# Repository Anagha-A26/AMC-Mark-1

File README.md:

# AMC-Mark-1
KiCad-based 2-layer STM32F401RE evaluation board with USB, UART, SPI, I²C, SWD, GPIO expansion, power regulation and user interfaces.

**STM32F401RE DEVELOPMENT BOARD**

**1. Selected MCU & Design Concept**

**Selected MCU**

**STM32F401RE / STM32F401RET6**

The **STM32F401RE** is selected as the core microcontroller for the evaluation board. It is based on an **Arm Cortex-M4 processor with Floating Point Unit (FPU)** and provides a broad set of peripherals, including GPIO, timers, ADC, UART/USART, SPI, I²C, USB 2.0 Full-Speed and SWD/JTAG debugging capabilities.
The MCU was selected because its peripheral set allows the major requirements of the evaluation board to be implemented around a **single central processing device**, while providing sufficient GPIO for external expansion.

**Why STM32F401RE?**

The core objective is to develop a **compact evaluation platform around the STM32F401RE** that allows users to:

- Program and debug the MCU through SWD.
- Communicate with a PC or USB host through USB.
- Experiment with UART, SPI and I²C peripherals.
- Access additional GPIOs for external circuits and modules.
- Interact with the board through user buttons and LEDs.
- Evaluate the MCU in a practical embedded-system development environment.

Thus, the STM32F401RE acts as the **central hub connecting the processing, communication, debugging and expansion interfaces**.

**Design Concept**

We propose a **compact, custom 2-layer STM32F401RE evaluation board** designed to provide convenient access to the MCU's processing, communication, debugging and GPIO capabilities.
The design is **functionally inspired by the STM32 NUCLEO-F401RE**, which provides STM32 development, Arduino compatibility, ST Morpho expansion and integrated ST-LINK debugging.
However, instead of reproducing the Nucleo architecture, our design independently implements the required functionality with a simpler and more focused architecture.

**Key design approach**

- **STM32F401RE** as the central MCU.
- **External ST-Link through SWD**, avoiding duplication of the on-board ST-LINK circuitry.
- **USB Type-C** providing direct USB 2.0 connectivity to the STM32.
- Dedicated and clearly labelled **UART, SPI and I²C interfaces**.
- **GPIO expansion headers** for external experimentation.
- Dedicated **reset button, user button, user LED and power indication**.
- Custom **power distribution, decoupling and grounding strategy**.
- Independently designed **2-layer PCB layout and routing** within the competition's 100 mm × 100 mm limit.

**Core Design Idea**

> To create a compact and accessible STM32F401RE evaluation platform that brings the MCU's major communication, debugging and GPIO capabilities onto a single independently designed 2-layer PCB, allowing users to program, debug and experiment with the MCU and external peripherals without reproducing the complete Nucleo architecture.

---

**Design Objectives**

1. Develop a functional **STM32F401RE evaluation platform**.
2. Provide **USB Type-C USB 2.0 connectivity** to the MCU.
3. Provide accessible **UART, SPI and I²C interfaces**.
4. Provide **SWD programming and debugging** using an external programmer/debugger.
5. Provide **user reset, user button, user LED and power indication**.
6. Provide **GPIO expansion headers** with power and ground.
7. Implement appropriate **power regulation and local decoupling**.
8. Develop a compact and electrically complete **2-layer PCB within 100 mm × 100 mm**.
9. Independently design the **schematic, component selection, placement, routing and silkscreen** rather than reproducing the reference board.

**2. BLOCK DIAGRAM**

**3. Schematic progress**

[View Schematic and PCB PDF](./schematic_pcb.pdf)

**4. Components Used**

| **Sl. No.** | **Component Type**     | **Value / Part Number**         | **Quantity** | **Section / Function**          |
| ----------- | ---------------------- | ------------------------------- | ------------ | ------------------------------- |
| 1           | Microcontroller        | STM32F401RET6                   | 1            | Main MCU                        |
| 2           | Voltage Regulator      | AMS1117-3.3                     | 1            | 5 V to 3.3 V regulation         |
| 3           | USB Type-C Connector   | USB\_C\_Receptacle\_USB2.0\_16P | 1            | USB communication and 5 V input |
| 4           | Pin Header / Connector | Conn\_01x02\_Pin                | 1            | External 5 V / GND connection   |
| 5           | Pin Header             | Conn\_01x05\_Pin                | 1            | SWD programming/debugging       |
| 6           | Pin Header             | Conn\_01x04\_Pin                | 1            | UART interface                  |
| 7           | Pin Header             | Conn\_01x06\_Pin                | 1            | SPI interface                   |
| 8           | Pin Header             | Conn\_01x04\_Pin                | 1            | I²C interface                   |
| 9           | Pin Header             | Conn\_01x10\_Pin                | 1            | GPIO expansion                  |
| 10          | Push Button            | SW\_Push                        | 1            | User button                     |
| 11          | Push Button            | SW\_Push                        | 1            | Reset button                    |
| 12          | LED                    | LED                             | 1            | Power ON indicator              |
| 13          | LED                    | LED                             | 1            | User-programmable LED           |
| 14          | Resistor               | 4.7 kΩ                          | 1            | I²C SCL pull-up                 |
| 15          | Resistor               | 4.7 kΩ                          | 1            | I²C SDA pull-up                 |
| 16          | Resistor               | 1 kΩ                            | 1            | Power LED current limiting      |
| 17          | Resistor               | 330 Ω                           | 1            | User LED current limiting       |
| 18          | Resistor               | 10 kΩ                           | 1            | BOOT0 pull-down                 |
| 19          | Resistor               | 10 kΩ                           | 1            | User button pull-up             |
| 20          | Resistor               | 10 kΩ                           | 1            | NRST pull-up                    |
| 21          | Resistor               | 5.1 kΩ                          | 1            | USB-C CC1 pull-down             |
| 22          | Resistor               | 5.1 kΩ                          | 1            | USB-C CC2 pull-down             |
| 23          | Capacitor              | 10 µF                           | 1            | AMS1117 input capacitor         |
| 24          | Capacitor              | 10 µF                           | 1            | AMS1117 output capacitor        |
| 25          | Power Multiplexer      | TPS2116DRLR                     | 1            | Priority selection between USB-C 5 V and external 5 V power inputs |

**5. Major design decisions**

- Selected USB Type-C as the USB connector for communication and power input.
- Designed the board to accept 5 V power from either USB-C or an external 5 V connector.
- Selected the AMS1117-3.3 voltage regulator to generate the required 3.3 V supply.
- Used an external ST-Link through the SWD header instead of including an onboard ST-Link debugger.
- Selected PA11 and PA12 for USB D− and D+ communication.
- Selected PA9 and PA10 for UART TX and RX.
- Selected PA4, PA5, PA6 and PA7 for SPI communication.
- Selected PB6 and PB7 for I²C communication.
- Used 4.7 kΩ pull-up resistors for the I²C SCL and SDA lines.
- Used 5.1 kΩ pull-down resistors on CC1 and CC2 to configure the USB-C connector for device operation.
- Pulled BOOT0 to GND using a 10 kΩ resistor to ensure normal boot from internal Flash memory.
- Used separate headers for UART, SPI, I²C, SWD and GPIO expansion for easier testing and external interfacing.
- Selected additional unused MCU pins and brought them out through a dedicated GPIO expansion header.
- Used separate Power ON LED and User LED to distinguish power status from software-controlled indication.
- Chose a simple push-button reset circuit with a pull-up resistor for reliable manual reset.

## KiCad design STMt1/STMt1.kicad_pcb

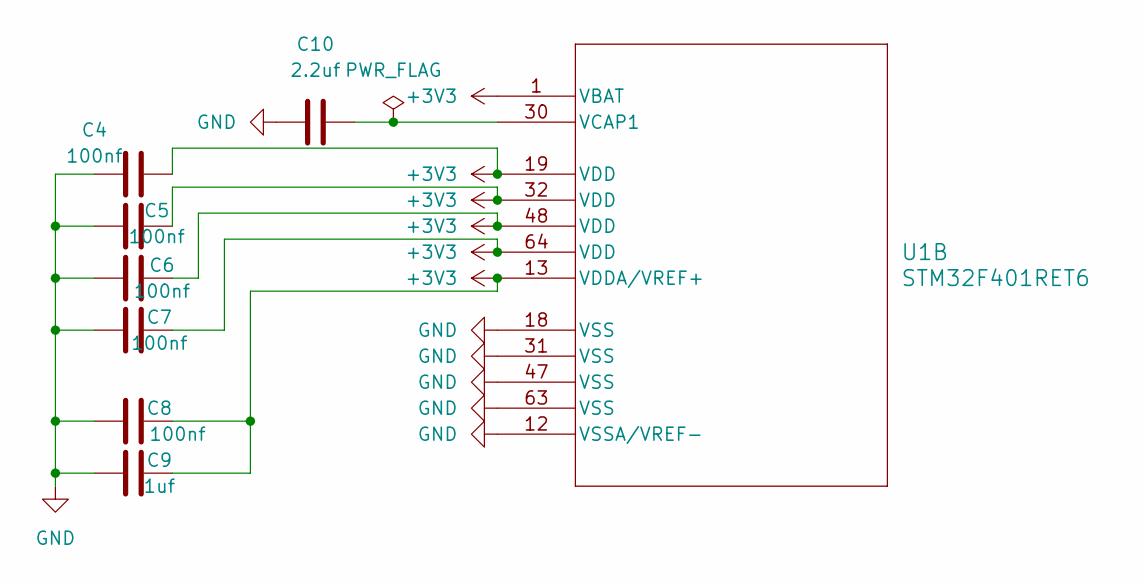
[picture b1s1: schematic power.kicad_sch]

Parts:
C4, C5, C6, C7, C8: 100nf; C_0603_1608Metric
C9: 1uf; C_0603_1608Metric
C10: 2.2uf; C_0603_1608Metric
U1: STM32F401RET6; QFP50P1200X1200X160-64N

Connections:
+3V3: C4.2, C5.2, C6.2, C7.2, C8.2, C9.2, U1.1 (VBAT), U1.13 (VDDA/VREF+), U1.19 (VDD), U1.32 (VDD), U1.48 (VDD), U1.64 (VDD); also elsewhere on the board
GND: C4.1, C5.1, C6.1, C7.1, C8.1, C9.1, C10.1, U1.12 (VSSA/VREF-), U1.18 (VSS), U1.31 (VSS), U1.47 (VSS), U1.63 (VSS); also elsewhere on the board
unnamed 36: C10.2, U1.30 (VCAP1); also elsewhere on the board

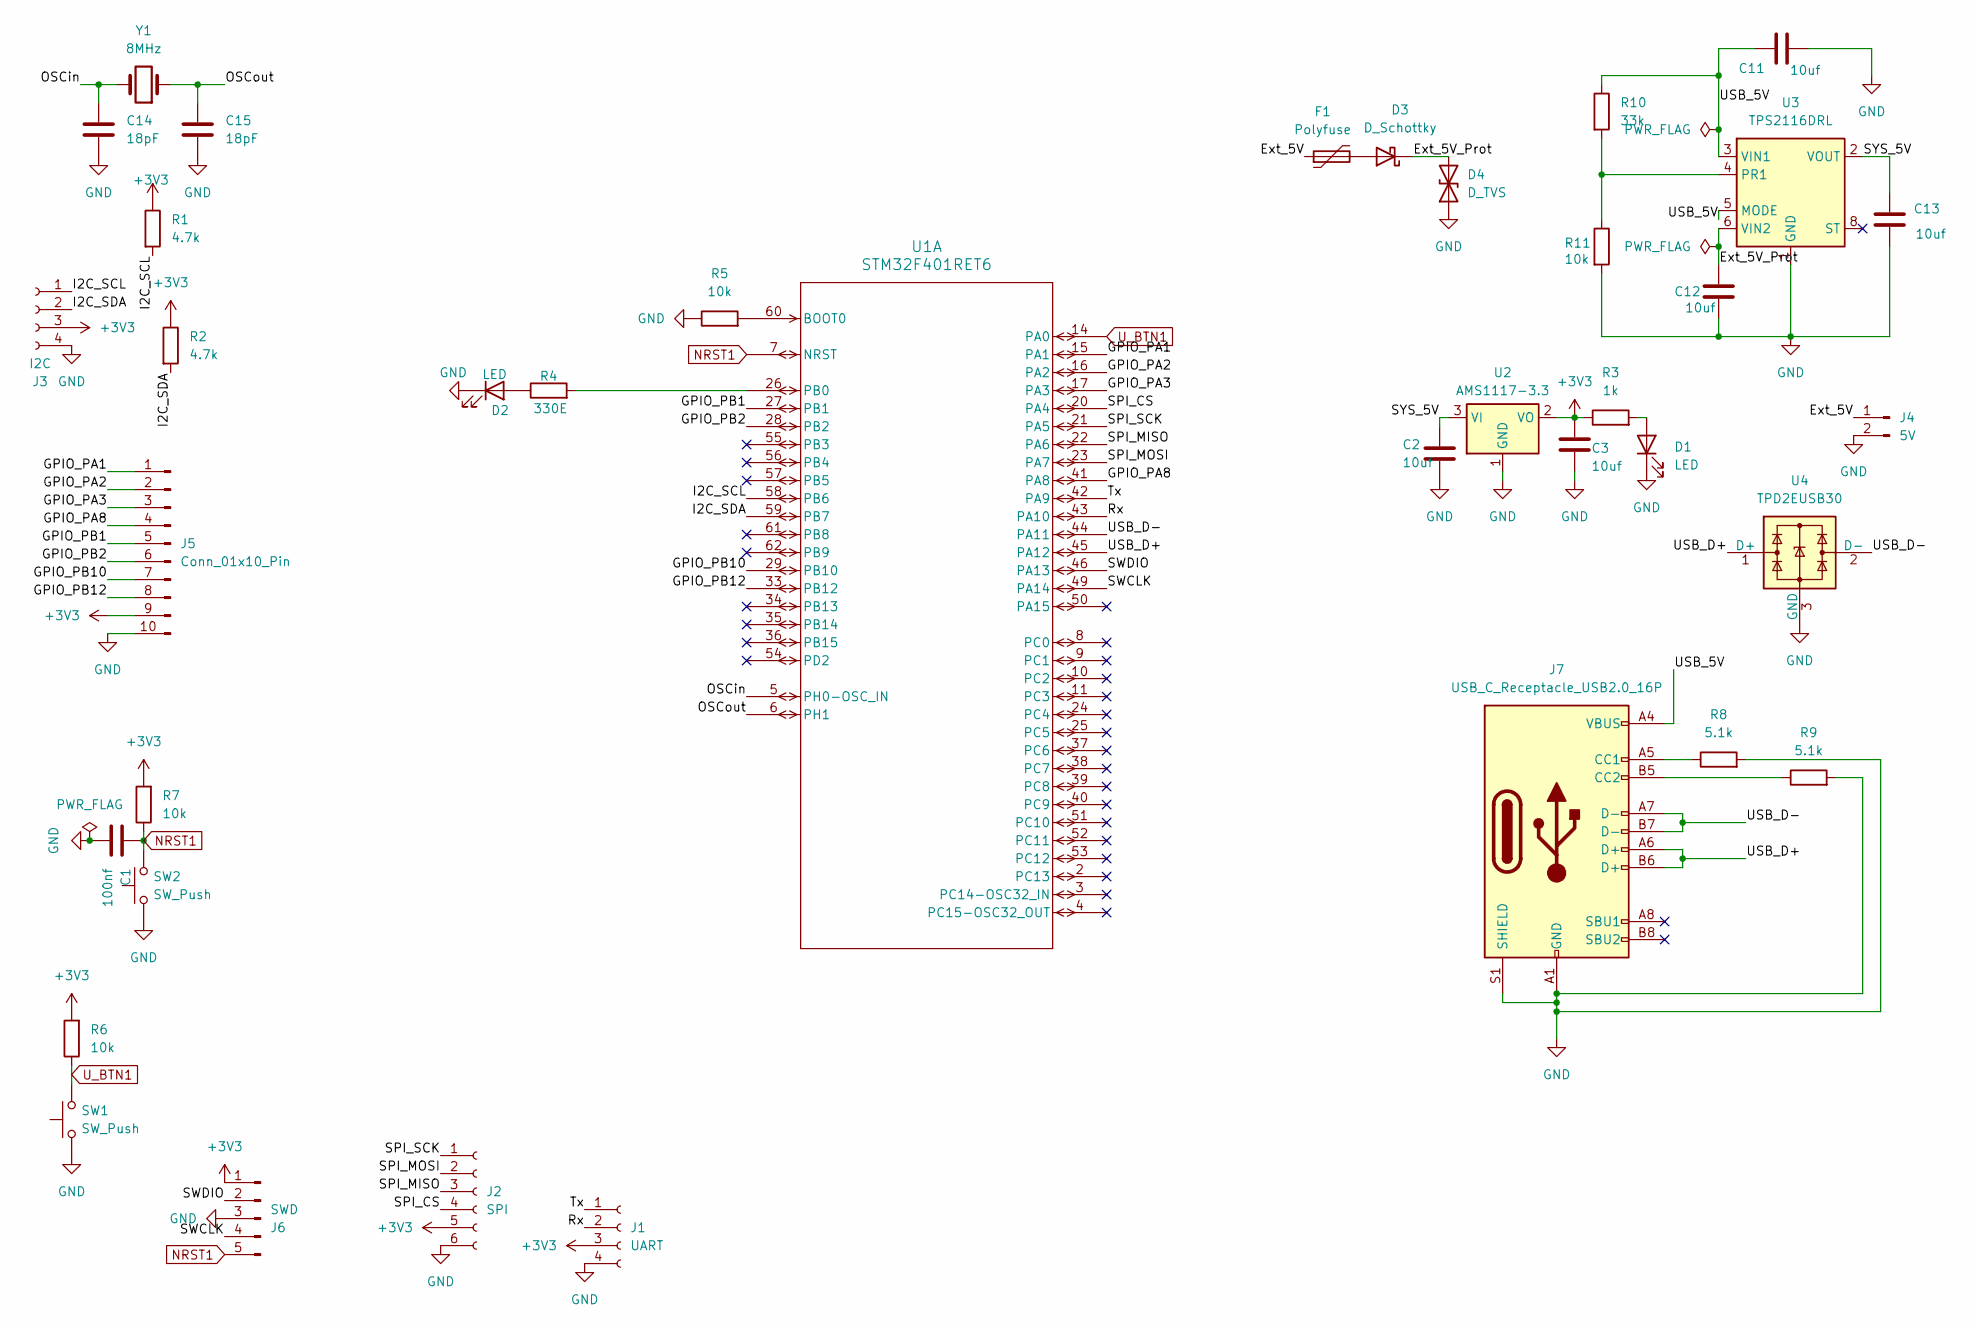
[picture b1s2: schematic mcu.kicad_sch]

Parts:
C1: 100nf; C_0603_1608Metric
C2, C3, C11, C12, C13: 10uf; C_0603_1608Metric
C14, C15: 18pF; C_0603_1608Metric
D1, D2: LED; LED_0603_1608Metric
D3: D_Schottky; SODFL3618X110N
D4: D_TVS; D_1206_3216Metric
F1: Polyfuse; Fuse_1206_3216Metric
J1: UART; PinSocket_1x04_P2.54mm_Vertical
J2: SPI; PinSocket_1x06_P2.54mm_Vertical
J3: I2C; PinSocket_1x04_P2.54mm_Vertical
J4: 5V; PinSocket_1x02_P2.54mm_Vertical
J5: Conn_01x10_Pin; PinSocket_1x10_P2.54mm_Vertical
J6: SWD; PinSocket_1x05_P2.54mm_Vertical
J7: USB_C_Receptacle_USB2.0_16P; USB_C_Receptacle_G-Switch_GT-USB-7010ASV
R1, R2: 4.7k; R_0603_1608Metric
R3: 1k; R_0603_1608Metric
R4: 330E; R_0603_1608Metric
R5, R6, R7, R11: 10k; R_0603_1608Metric
R8, R9: 5.1k; R_0603_1608Metric
R10: 33k; R_0603_1608Metric
SW1, SW2: SW_Push; SW_Push_1P1T_NO_CK_KMR2
U1: STM32F401RET6; QFP50P1200X1200X160-64N
U2: AMS1117-3.3; SOT-223-3_TabPin2
U3: TPS2116DRL; SOTFL50P160X60-8N
U4: TPD2EUSB30; SOTFL35P100X50-3N
Y1: 8MHz; Crystal_SMD_0603-2Pin_6.0x3.5mm

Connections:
+3V3: C3.1, J1.3, J2.5, J3.3, J5.9, J6.1, R1.1, R2.1, R3.1, R6.2, R7.2, U2.2 (VO); also elsewhere on the board
/MCU/Ext_5V: F1.1, J4.1
/MCU/Ext_5V_Prot: C12.1, D3.1 (K), D4.2 (A2), U3.6 (VIN2)
/MCU/GPIO_PA1: J5.1, U1.15 (PA1); also elsewhere on the board
/MCU/GPIO_PA2: J5.2, U1.16 (PA2); also elsewhere on the board
/MCU/GPIO_PA3: J5.3, U1.17 (PA3); also elsewhere on the board
/MCU/GPIO_PA8: J5.4, U1.41 (PA8); also elsewhere on the board
/MCU/GPIO_PB1: J5.5, U1.27 (PB1); also elsewhere on the board
/MCU/GPIO_PB2: J5.6, U1.28 (PB2); also elsewhere on the board
/MCU/GPIO_PB10: J5.7, U1.29 (PB10); also elsewhere on the board
/MCU/GPIO_PB12: J5.8, U1.33 (PB12); also elsewhere on the board
/MCU/I2C_SCL: J3.1, R1.2, U1.58 (PB6); also elsewhere on the board
/MCU/I2C_SDA: J3.2, R2.2, U1.59 (PB7); also elsewhere on the board
/MCU/OSCin: C14.1, U1.5 (PH0-OSC_IN), Y1.2; also elsewhere on the board
/MCU/OSCout: C15.1, U1.6 (PH1), Y1.1; also elsewhere on the board
/MCU/Rx: J1.2, U1.43 (PA10); also elsewhere on the board
/MCU/SPI_CS: J2.4, U1.20 (PA4); also elsewhere on the board
/MCU/SPI_MISO: J2.3, U1.22 (PA6); also elsewhere on the board
/MCU/SPI_MOSI: J2.2, U1.23 (PA7); also elsewhere on the board
/MCU/SPI_SCK: J2.1, U1.21 (PA5); also elsewhere on the board
/MCU/SWCLK: J6.4, U1.49 (PA14); also elsewhere on the board
/MCU/SWDIO: J6.2, U1.46 (PA13); also elsewhere on the board
/MCU/SYS_5V: C2.1, C13.1, U2.3 (VI), U3.2 (VOUT), U3.7 (VOUT)
/MCU/Tx: J1.1, U1.42 (PA9); also elsewhere on the board
/MCU/USB_5V: C11.1, J7.A4 (VBUS), J7.A9 (VBUS), J7.B4 (VBUS), J7.B9 (VBUS), R10.1, U3.3 (VIN1), U3.5 (MODE)
/MCU/USB_D+: J7.A6 (D+), J7.B6 (D+), U1.45 (PA12), U4.1 (D+); also elsewhere on the board
/MCU/USB_D-: J7.A7 (D-), J7.B7 (D-), U1.44 (PA11), U4.2 (D-); also elsewhere on the board
GND: C1.2, C2.2, C3.2, C11.2, C12.2, C13.2, C14.2, C15.2, D1.1 (K), D2.1 (K), D4.1 (A1), J1.4, J2.6, J3.4, J4.2, J5.10, J6.3, J7.A1 (GND), J7.A12 (GND), J7.B1 (GND), J7.B12 (GND), J7.S1 (SHIELD), R5.1, R8.2, R9.2, R11.2, SW1.1, SW2.1, U2.1 (GND), U3.1 (GND), U4.3 (GND); also elsewhere on the board
NRST1: C1.1, J6.5, R7.1, SW2.2, U1.7 (NRST); also elsewhere on the board
unnamed: D1.2 (A), R3.2
unnamed: D2.2 (A), R4.1
unnamed: D3.2 (A), F1.2
unnamed: J7.A5 (CC1), R8.1
unnamed: J7.B5 (CC2), R9.1
unnamed 34: R5.2, U1.60 (BOOT0); also elsewhere on the board
unnamed 35: R4.2, U1.26 (PB0); also elsewhere on the board
unnamed: R10.2, R11.1, U3.4 (PR1)
U_BTN1: R6.1, SW1.2, U1.14 (PA0); also elsewhere on the board

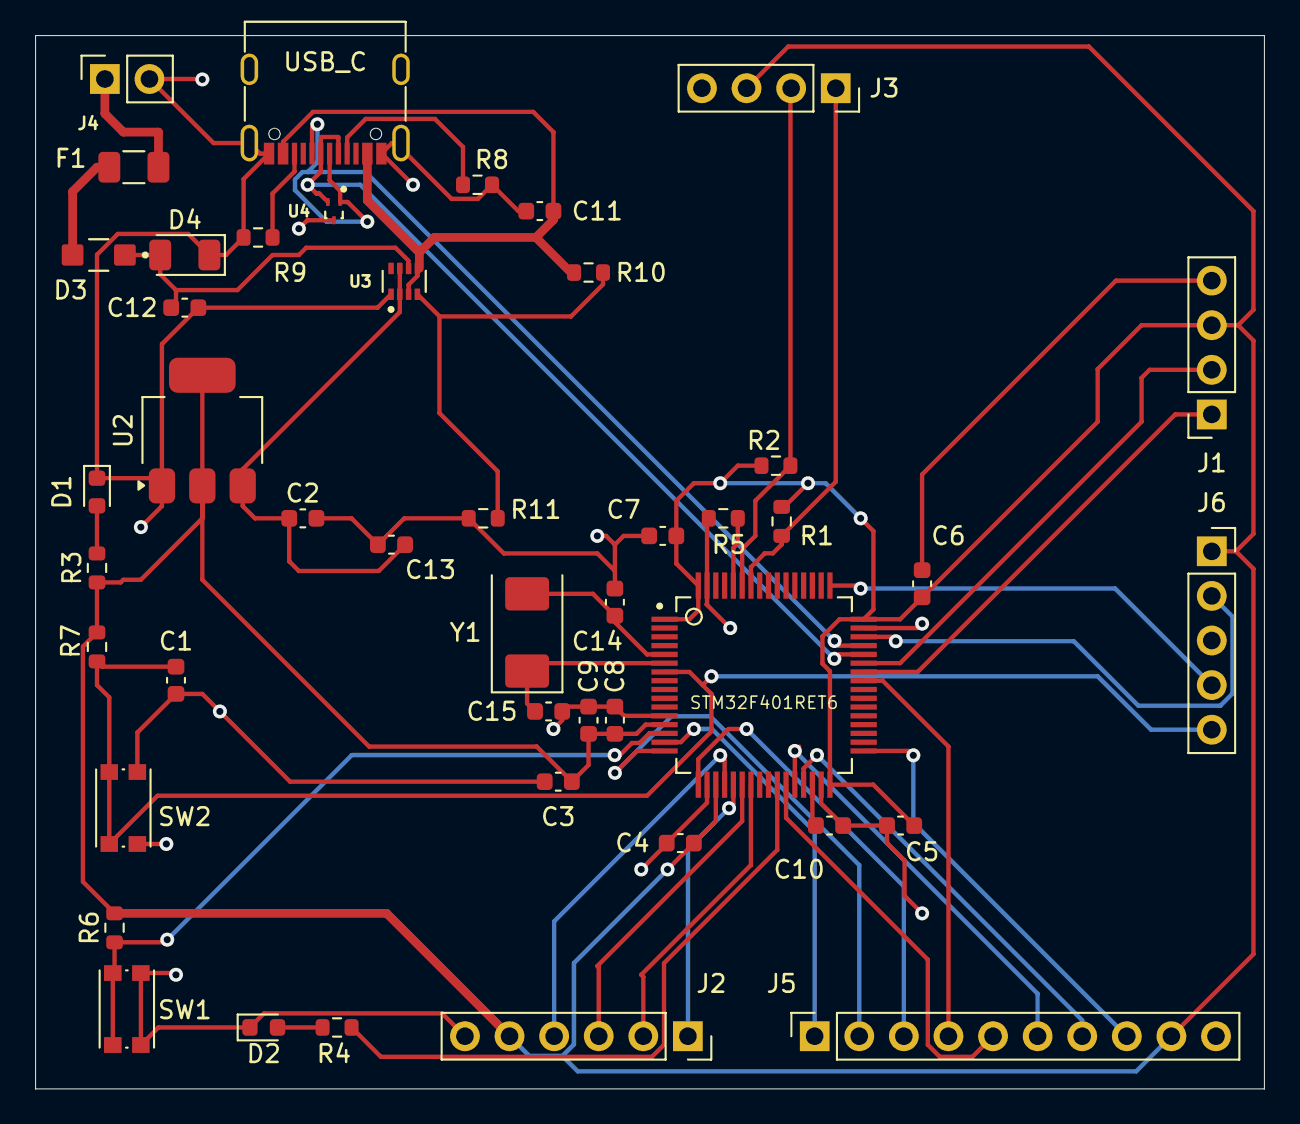
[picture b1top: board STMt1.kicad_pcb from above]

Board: 2 copper layers, 70.0 x 60.0 mm, 45 parts (0 on the bottom side), 39 nets.

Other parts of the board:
STM32F401RET6: U1; QFP50P1200X1200X160-64N

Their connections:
+3V3: STM32F401RET6.1 (VBAT), STM32F401RET6.13 (VDDA/VREF+), STM32F401RET6.19 (VDD), STM32F401RET6.32 (VDD), STM32F401RET6.48 (VDD), STM32F401RET6.64 (VDD); also elsewhere on the board
/MCU/GPIO_PA1: STM32F401RET6.15 (PA1); also elsewhere on the board
/MCU/GPIO_PA2: STM32F401RET6.16 (PA2); also elsewhere on the board
/MCU/GPIO_PA3: STM32F401RET6.17 (PA3); also elsewhere on the board
/MCU/GPIO_PA8: STM32F401RET6.41 (PA8); also elsewhere on the board
/MCU/GPIO_PB1: STM32F401RET6.27 (PB1); also elsewhere on the board
/MCU/GPIO_PB2: STM32F401RET6.28 (PB2); also elsewhere on the board
/MCU/GPIO_PB10: STM32F401RET6.29 (PB10); also elsewhere on the board
/MCU/GPIO_PB12: STM32F401RET6.33 (PB12); also elsewhere on the board
/MCU/I2C_SCL: STM32F401RET6.58 (PB6); also elsewhere on the board
/MCU/I2C_SDA: STM32F401RET6.59 (PB7); also elsewhere on the board
/MCU/OSCin: STM32F401RET6.5 (PH0-OSC_IN); also elsewhere on the board
/MCU/OSCout: STM32F401RET6.6 (PH1); also elsewhere on the board
/MCU/Rx: STM32F401RET6.43 (PA10); also elsewhere on the board
/MCU/SPI_CS: STM32F401RET6.20 (PA4); also elsewhere on the board
/MCU/SPI_MISO: STM32F401RET6.22 (PA6); also elsewhere on the board
/MCU/SPI_MOSI: STM32F401RET6.23 (PA7); also elsewhere on the board
/MCU/SPI_SCK: STM32F401RET6.21 (PA5); also elsewhere on the board
/MCU/SWCLK: STM32F401RET6.49 (PA14); also elsewhere on the board
/MCU/SWDIO: STM32F401RET6.46 (PA13); also elsewhere on the board
/MCU/Tx: STM32F401RET6.42 (PA9); also elsewhere on the board
/MCU/USB_D+: STM32F401RET6.45 (PA12); also elsewhere on the board
/MCU/USB_D-: STM32F401RET6.44 (PA11); also elsewhere on the board
GND: STM32F401RET6.12 (VSSA/VREF-), STM32F401RET6.18 (VSS), STM32F401RET6.31 (VSS), STM32F401RET6.47 (VSS), STM32F401RET6.63 (VSS); also elsewhere on the board
NRST1: STM32F401RET6.7 (NRST); also elsewhere on the board
unnamed 34: STM32F401RET6.60 (BOOT0); also elsewhere on the board
unnamed 35: STM32F401RET6.26 (PB0); also elsewhere on the board
unnamed 36: STM32F401RET6.30 (VCAP1); also elsewhere on the board
U_BTN1: STM32F401RET6.14 (PA0); also elsewhere on the board

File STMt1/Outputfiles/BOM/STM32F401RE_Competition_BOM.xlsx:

STM32F401RE Evaluation Board – Competition BOM
AMC Mark 1 Estimated component cost in INR
Reference | Qty | Value / Part | Footprint | Unit Cost (₹) | Total Cost (₹) | Price Basis / Note
C1,C4,C5,C6,C7,C8 | 6 | 100nF | Capacitor_SMD:C_0603_1608Metric | 0.5 | 3 | Indicative India component price
C2,C3,C11,C12,C13 | 5 | 10uF | Capacitor_SMD:C_0603_1608Metric | 1.5 | 7.5 | Indicative India component price
C9 | 1 | 1uF | Capacitor_SMD:C_0603_1608Metric | 0.6 | 0.6 | Indicative India component price
C10 | 1 | 2.2uF | Capacitor_SMD:C_0603_1608Metric | 0.8 | 0.8 | Indicative India component price
C14,C15 | 2 | 18pF | Capacitor_SMD:C_0603_1608Metric | 0.5 | 1 | Indicative India component price
D1,D2 | 2 | LED | LED_SMD:LED_0603_1608Metric | 1 | 2 | Indicative India component price
D3 | 1 | 1N5819W Schottky | 1N5819W:SODFL3618X110N | 3 | 3 | Indicative India component price
D4 | 1 | D_TVS | Diode_SMD:D_1206_3216Metric | 7 | 7 | Indicative India component price
F1 | 1 | Polyfuse | Fuse:Fuse_1206_3216Metric | 5 | 5 | Indicative India component price
J1 | 1 | UART | 1x04 2.54mm vertical header | 4 | 4 | Indicative India component price
J2 | 1 | SPI | 1x06 2.54mm vertical header | 6 | 6 | Indicative India component price
J3 | 1 | I2C | 1x04 2.54mm vertical header | 4 | 4 | Indicative India component price
J4 | 1 | 5V | 1x02 2.54mm vertical header | 2.5 | 2.5 | Indicative India component price
J5 | 1 | GPIO Expansion | 1x10 2.54mm vertical header | 10 | 10 | Indicative India component price
J6 | 1 | SWD | 1x05 2.54mm vertical header | 5 | 5 | Indicative India component price
J7 | 1 | GT-USB-7010ASV USB-C | Connector_USB:USB_C_Receptacle_G-Switch_GT-USB-7010ASV | 8 | 8 | LCSC listing indicates low-cost part; ₹8 used as practical India estimate
R1,R2 | 2 | 4.7k | Resistor_SMD:R_0603_1608Metric | 0.25 | 0.5 | Indicative India component price
R3 | 1 | 1k | Resistor_SMD:R_0603_1608Metric | 0.25 | 0.25 | Indicative India component price
R4 | 1 | 330E | Resistor_SMD:R_0603_1608Metric | 0.25 | 0.25 | Indicative India component price
R5,R6,R7,R11 | 4 | 10k | Resistor_SMD:R_0603_1608Metric | 0.25 | 1 | Indicative India component price
R8,R9 | 2 | 5.1k | Resistor_SMD:R_0603_1608Metric | 0.25 | 0.5 | Indicative India component price
R10 | 1 | 33k | Resistor_SMD:R_0603_1608Metric | 0.25 | 0.25 | Indicative India component price
SW1,SW2 | 2 | SW_Push / KMR2 | Button_Switch_SMD:SW_Push_1P1T_NO_CK_KMR2 | 45 | 90 | C&K KMR2 class; ₹45 used as practical estimate
U1 | 1 | STM32F401RET6 | STM32F401RET6:QFP50P1200X1200X160-64N | 714.69 | 714.69 | Mouser India, 1-piece indicative price
U2 | 1 | AMS1117-3.3 | Package_TO_SOT_SMD:SOT-223-3_TabPin2 | 4.9000000000000004 | 4.9000000000000004 | Indian distributor indicative price
U3 | 1 | TPS2116DRL | TPS2116DRLR:SOTFL50P160X60-8N | 45 | 45 | Indicative India component price
U4 | 1 | TPD2EUSB30ADRTR | TPD2EUSB30ADRTR:SOTFL35P100X50-3N | 94.11 | 94.11 | Mouser/DigiKey India 1-piece indicative price
Y1 | 1 | 8MHz | Crystal:Crystal_SMD_0603-2Pin_6.0x3.5mm | 8 | 8 | Indicative India component price
 |  |  |  | GRAND TOTAL | 1028.8499999999999
Submission Notes
• This BOM is based on the user's exported KiCad BOM (STMt1.csv).
• Prices are estimated component costs for competition documentation, not a sup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
• Major IC prices were checked against current Indian distributor listings wher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
• PCB fabrication, assembly, shipping, and taxes are NOT included in the compon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
• For final procurement, replace estimates with supplier quotations/invoices if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
